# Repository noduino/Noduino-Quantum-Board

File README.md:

# Noduino-Quantum-Board
Noduino Quantum ESP32 Dev Board

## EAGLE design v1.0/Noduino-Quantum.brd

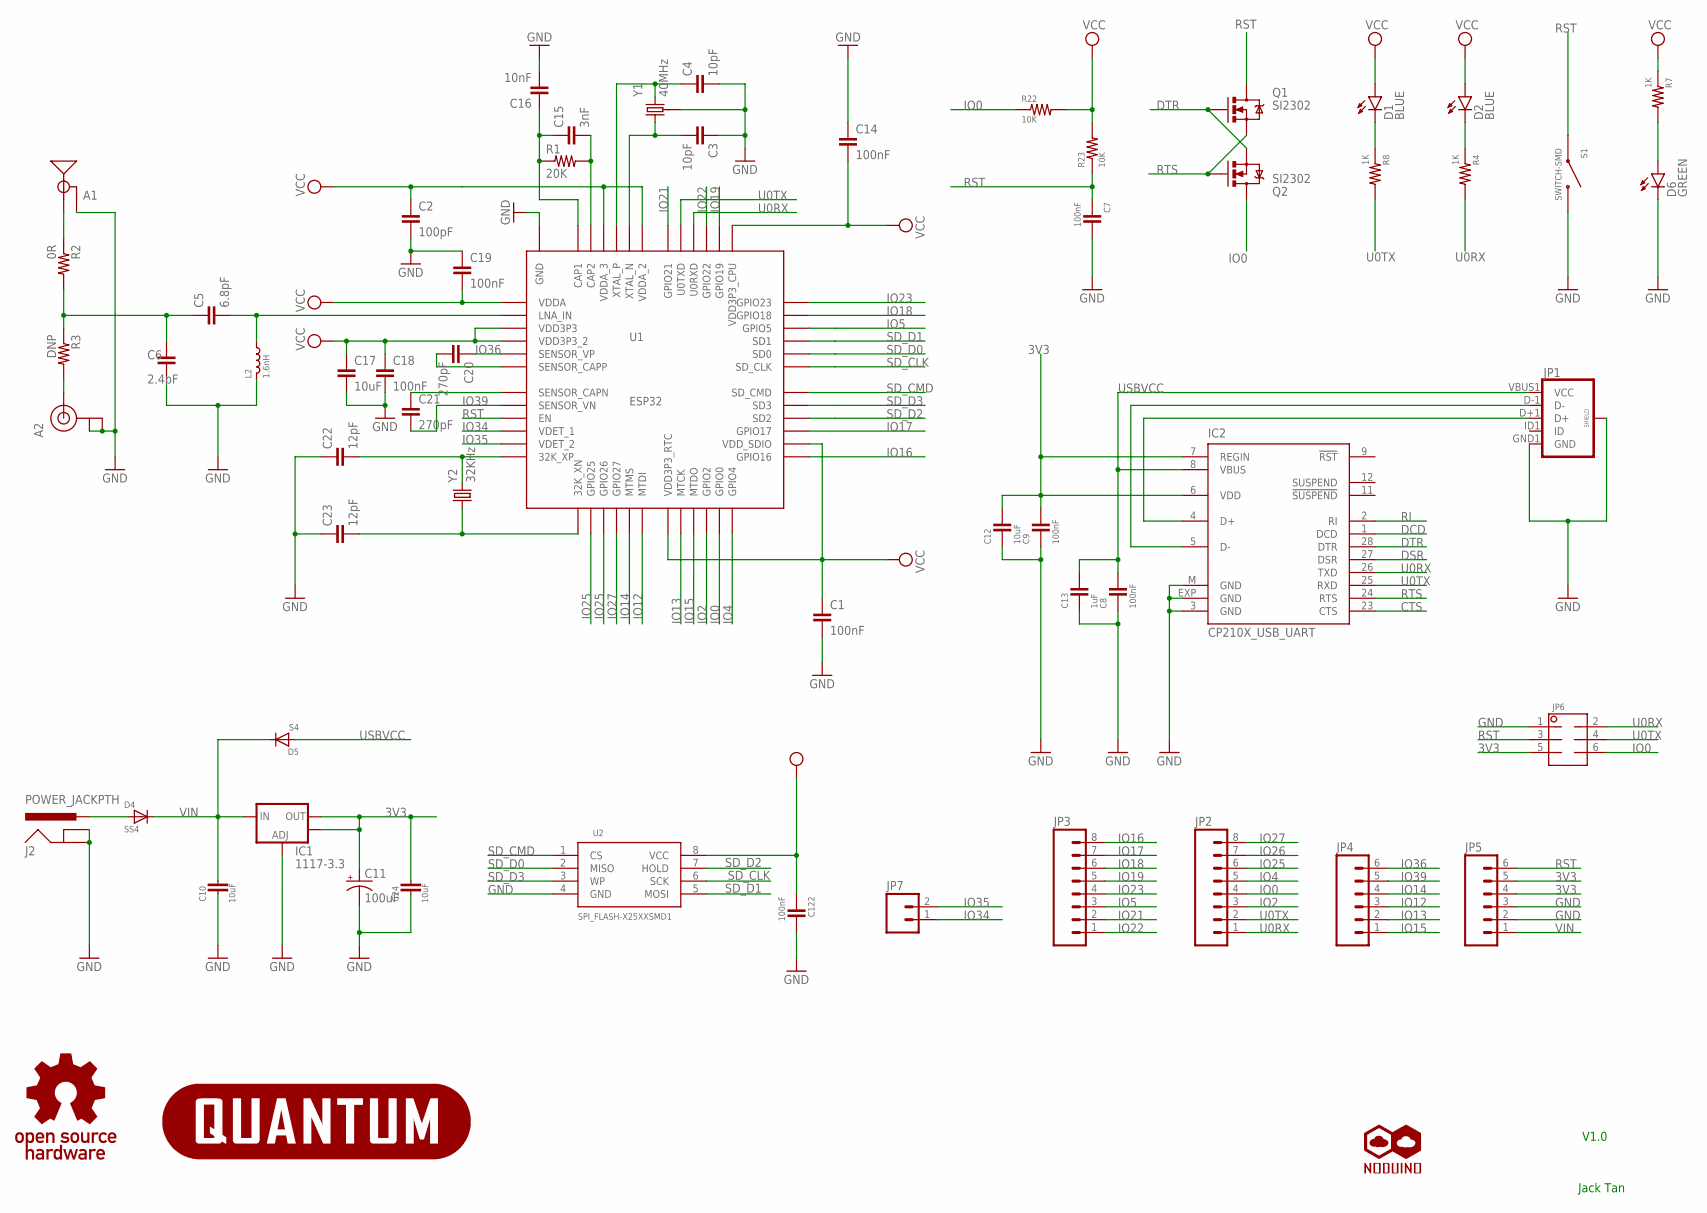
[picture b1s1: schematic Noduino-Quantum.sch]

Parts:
A1: ANTENNATPLACE; TRACE_ANTENNA_2.4GHZ_15.2MM_TPLACE
A2: U.FL
C1, C7, C14, C18, C19, C122: 100nF; 0402-CAP
C2: 100pF; 0402-CAP
C3, C4: 10pF; 0402-CAP
C5: 6.8pF; 0402-CAP
C6: 2.4pF; 0402-CAP
C8, C9: 100nF; 0603-CAP
C10, C24: 10uF; C1206
C11: 100uF; EIA3528
C12, C17: 10uF; 0603-CAP
C13: 1uF; 0603-CAP
C15: 3nF; 0402-CAP
C16: 10nF; 0402-CAP
C20, C21: 270pF; 0402-CAP
C22, C23: 12pF; 0402-CAP
D1, D2: BLUE; LED-0603
D4: SS4; DO214
D5: S4; SOD-323
D6: GREEN; LED-0603
IC1: 1117-3.3; SOT223
IC2: CP210X_USB_UART; MLP28
J2: POWER_JACKPTH; POWER_JACK_PTH
JP1: USB_MICROB_PLUG; MICROUSB-SMD-DIP
JP2, JP3: M081X08; 1X08
JP4, JP5: M06SIP; 1X06
JP6: M02X3; 2X3
JP7: M02PTH; 1X02
L2: 1.6nH; 0402-IND
Q1, Q2: SI2302; SOT23-3
R1: 20K; 0402-RES
R2: 0R; 0402-RES
R3: DNP; 0402-RES
R4, R7, R8: 1K; 0603-RES
R22: 10K; 0603-RES
R23: 10K; 0402-RES
S1: SWITCH-SMD; TACTILE-SWITCH-1101NE
U1: ESP32; QFN48-0.4MM
U2: SPI_FLASH-X25XXSMD1; SO08-EIAJ
U$1: NODUINO-LOGO-ALL; NODUINO-ALL-1
U$2: NODUINO-QUANTUM-LOGO
U$3: OPEN_HARDWARE_LOGO
Y1: 40MHz; 2520-CRY
Y2: 32KHz; CRYSTAL-32KHZ-MS3V

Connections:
3V3: C1.1, C2.1, C9.2, C11.A (+), C12.2, C14.2, C17.1, C18.1, C19.2, C24.1, C122.1, D1.A, D2.A, IC1.2 (OUT), IC1.4 (OUT), IC2.6 (VDD), IC2.7 (REGIN), JP5.4, JP5.5, JP6.5, R7.1, R22.2, R23.2, U1.1 (VDDA), U1.3 (VDD3P3), U1.4 (VDD3P3_2), U1.19 (VDD3P3_RTC), U1.26 (VDD_SDIO), U1.37 (VDD3P3_CPU), U1.43 (VDDA_2), U1.46 (VDDA_3), U2.8 (VCC)
CTS: IC2.23 (CTS)
DCD: IC2.1 (DCD)
DSR: IC2.27 (DSR)
DTR: IC2.28 (DTR), Q1.1 (G), Q2.2 (S)
GND: A1.GND, A2.P$1 (GND), A2.P$2 (GND), C1.2, C2.2, C3.1, C4.2, C6.2, C7.2, C8.1, C9.1, C10.2, C11.C (-), C12.1, C13.1, C14.1, C16.2, C17.2, C18.2, C19.1, C22.1, C23.1, C24.2, C122.2, D6.C, IC1.1 (ADJ), IC2.3 (GND), IC2.EXP (GND), IC2.M (GND), J2.GND, J2.GNDBREAK, JP1.GND1 (GND), JP1.P$1 (SHIELD), JP1.P$2 (SHIELD), JP1.P$3 (SHIELD), JP1.P$4 (SHIELD), JP5.2, JP5.3, JP6.1, L2.1 (X1), S1.P$1 (1), U1.EP (GND), U2.4 (GND), Y1.2 (GND), Y1.4 (GND)
IO0: JP2.4, JP6.6, Q2.3 (D), R22.1, U1.23 (GPIO0)
IO2: JP2.3, U1.22 (GPIO2)
IO4: JP2.5, U1.24 (GPIO4)
IO5: JP3.3, U1.34 (GPIO5)
IO12: JP4.3, U1.18 (MTDI)
IO13: JP4.2, U1.20 (MTCK)
IO14: JP4.4, U1.17 (MTMS)
IO15: JP4.1, U1.21 (MTDO)
IO16: JP3.8, U1.25 (GPIO16)
IO17: JP3.7, U1.27 (GPIO17)
IO18: JP3.6, U1.35 (GPIO18)
IO19: JP3.5, U1.38 (GPIO19)
IO21: JP3.2, U1.42 (GPIO21)
IO22: JP3.1, U1.39 (GPIO22)
IO23: JP3.4, U1.36 (GPIO23)
IO25: JP2.6, U1.14 (GPIO25)
IO26: JP2.7, U1.15 (GPIO26)
IO27: JP2.8, U1.16 (GPIO27)
IO34: JP7.1, U1.10 (VDET_1)
IO35: JP7.2, U1.11 (VDET_2)
IO36: C20.1, JP4.6, U1.5 (SENSOR_VP)
IO39: C21.2, JP4.5, U1.8 (SENSOR_VN)
LNA: C5.2, L2.2 (X2), U1.2 (LNA_IN)
unnamed: D1.C, R8.1
unnamed: C4.1, U1.45 (XTAL_P), Y1.3 (2)
unnamed: C3.2, U1.44 (XTAL_N), Y1.1
unnamed: IC2.4 (D+), JP1.D+1 (D+)
unnamed: A1.ANT (SIGNAL), R2.1
unnamed: IC2.5 (D-), JP1.D-1 (D-)
unnamed: C15.2, R1.2, U1.47 (CAP2)
unnamed: D2.C, R4.1
unnamed: D6.A, R7.2
unnamed: D4.A, J2.PWR
unnamed: C15.1, C16.1, R1.1, U1.48 (CAP1)
unnamed: A2.P$3 (SIGNAL), R3.2
unnamed: C5.1, C6.1, R3.1
unnamed: C21.1, U1.7 (SENSOR_CAPN)
unnamed: C20.2, U1.6 (SENSOR_CAPP)
unnamed: C22.2, U1.12 (32K_XP), Y2.P$2 (2)
unnamed: C23.2, U1.13 (32K_XN), Y2.P$1 (1)
RI: IC2.2 (RI)
RST: C7.1, JP5.6, JP6.3, Q1.3 (D), R23.1, S1.P$2 (2), U1.9 (EN)
RTS: IC2.24 (RTS), Q1.2 (S), Q2.1 (G)
SD_CLK: U1.31 (SD_CLK), U2.6 (SCK)
SD_CMD: U1.30 (SD_CMD), U2.1 (CS)
SD_D0: U1.32 (SD0), U2.2 (MISO)
SD_D1: U1.33 (SD1), U2.5 (MOSI)
SD_D2: U1.28 (SD2), U2.7 (HOLD)
SD_D3: U1.29 (SD3), U2.3 (WP)
U0RX: IC2.26 (TXD), JP2.1, JP6.2, R4.2, U1.40 (U0RXD)
U0TX: IC2.25 (RXD), JP2.2, JP6.4, R8.2, U1.41 (U0TXD)
USBVCC: C8.2, C13.2, D5.2 (A), IC2.8 (VBUS), JP1.VBUS1 (VCC)
VIN: C10.1, D4.C, D5.1 (C), IC1.3 (IN), JP5.1

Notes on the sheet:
Jack Tan
V1.0

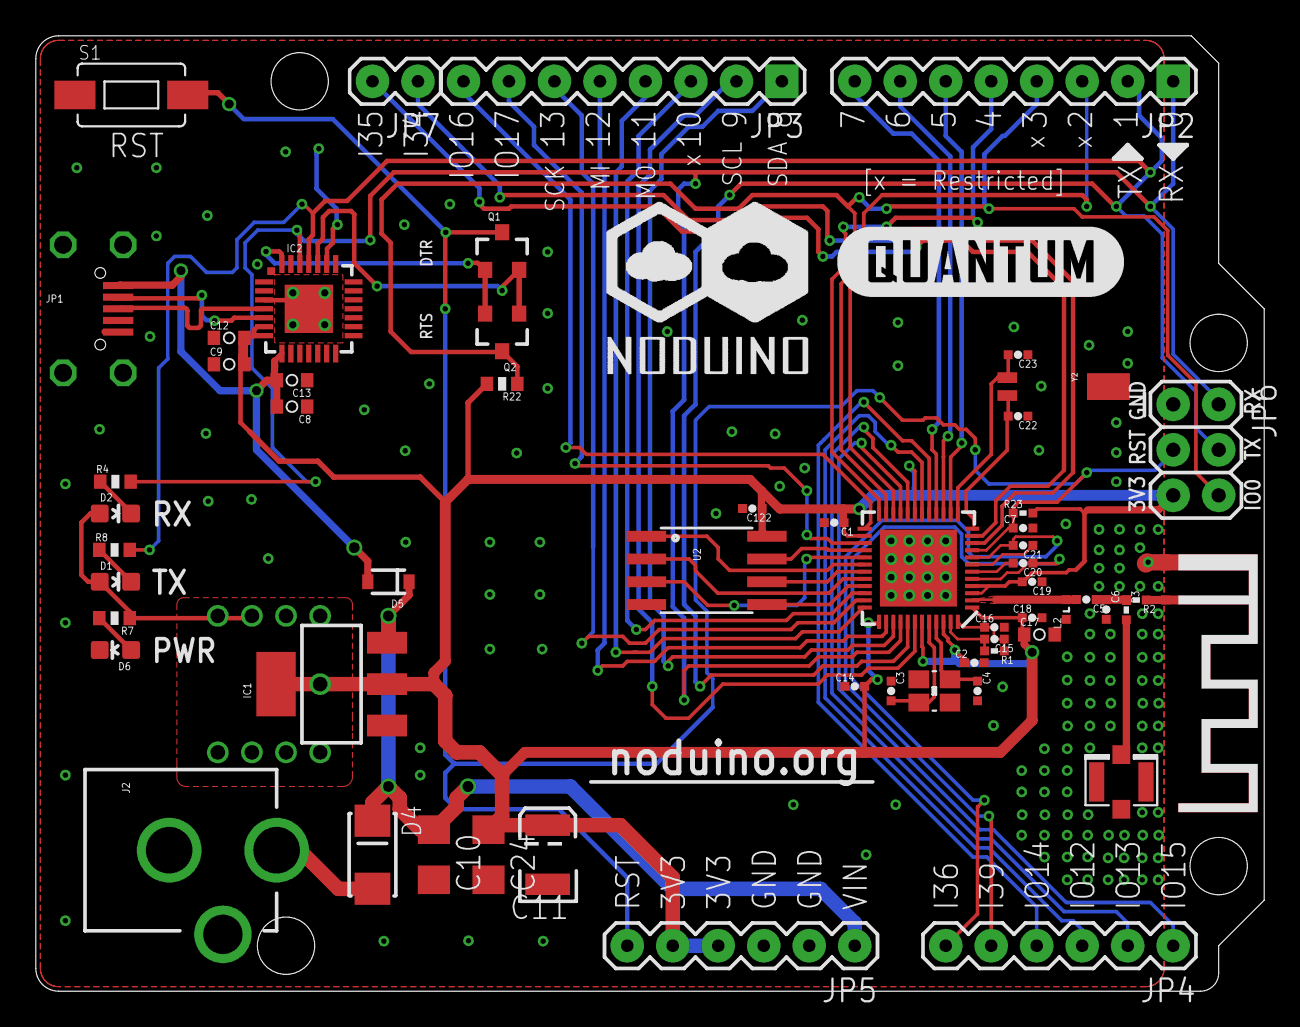
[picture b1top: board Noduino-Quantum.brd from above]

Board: 2 copper layers, 68.6 x 53.3 mm, 61 parts (1 on the bottom side), 55 nets.

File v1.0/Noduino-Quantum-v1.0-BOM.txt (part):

Partlist exported from C:/Users/Jack/Documents/eagle/Noduino/Quantum/V1.0/Noduino-Quantum.sch at 2016/11/1 20:32:44

Part Value                Device               Package                            Description                                                             PROD_ID    VALUE
A1                        ANTENNATPLACE        TRACE_ANTENNA_2.4GHZ_15.2MM_TPLACE Chip antenna                                                                            
A2   U.FL                 U.FL                 U.FL                               SMD antenna connector- WRL-09144                                        CONN-09193 U.FL
 
C1   100nF                0402-CAP             0402-CAP                                                                                                                   

C2   100pF                0402-CAP             0402-CAP                                                                                                                   

C3   15pF                 0402-CAP             0402-CAP                                                                                                                   
C4   15pF                 0402-CAP             0402-CAP                                                                                                                   

C5   6.8pF                0402-CAP             0402-CAP                                                                                                                   
C6   2.4pF                0402-CAP             0402-CAP                                                                                                                   

C7   100nF                0402-CAP             0402-CAP
                                                                                                                   
C8   100nF                0603-CAP             0603-CAP                                                                                                                   
C9   100nF                0603-CAP             0603-CAP
                                                                                                                   
C10  10uF                 CAP-C1206            C1206                              Capacitor                                                                               
C11  100uF                CAP_POL3528          EIA3528                            Capacitor Polarized
                                                                     
C12  10uF                 0603-CAP             0603-CAP                                                                                                                   
C13  1uF                  0603-CAP             0603-CAP 
                                                                                                                  
C14  100nF                0402-CAP             0402-CAP                                                                                                                   

C15  3nF                  0402-CAP             0402-CAP                                                                                                                   
C16  10nF                 0402-CAP             0402-CAP                                                                                                                   

C17  10uF                 0603-CAP             0603-CAP                                                                                                                   

C18  100nF                0402-CAP             0402-CAP                                                                                                                   
C19  100nF                0402-CAP             0402-CAP                                                                                                                   

C20  270pF                0402-CAP             0402-CAP                                                                                                                   
C21  270pF                0402-CAP             0402-CAP                                                                                                                   
C22  12pF                 0402-CAP             0402-CAP                                                                                                                   
C23  12pF                 0402-CAP             0402-CAP

C24  10uF                 CAP-C1206            C1206                              Capacitor    
                                                                           
C122 100nF                0402-CAP             0402-CAP                                                                                                                   

D1   BLUE                 LED-GREEN0603        LED-0603                           Various green LEDs                                                      DIO-00821  GREEN
D2   BLUE                 LED-GREEN0603        LED-0603                           Various green LEDs                                                      DIO-00821  GREEN

D4   S7                   DIODEHV              DO214                              Diode                                                                                   
D5   S4                   DIODESOD             SOD-323                            Diode                                                                                   

D6   GREEN                LED-GREEN0603        LED-0603                           Various green LEDs                                                      DIO-00821  GREEN

IC1  1117-3.3             AMS1117SOT223        SOT223                             Voltage Regulator LM1117                                                                
IC2  CP210X_USB_UART      CP210X_USB_UART      MLP28                              Single-Chip USB to UART Bridge
                                                         
J2   POWER_JACKPTH        POWER_JACKPTH        POWER_JACK_PTH                     Power Jack                                                                              
JP1                       USB_MICROB_PLUG      MICROUSB-SMD-DIP                   USB Micro-B connectors 
                                                                 
JP2  M081X08              M081X08              1X08                               Header 8                                                                                
JP3  M081X08              M081X08              1X08                               Header 8                                                                                
JP4  M06SIP               M06SIP               1X06                               Header 6                                                                                
JP5  M06SIP               M06SIP               1X06                               Header 6                                                                                
JP6  M02X3                M02X3                2X3                                                                                                                        
JP7                       M02PTH               1X02                               Header 2
                                                                                
L2   1.6nH                INDUCTOR0402         0402-IND
                                                                                                                   
Q1   SI2302               -MOSFET-N-SMD        SOT23-3                                                                                                                    
Q2   SI2302               -MOSFET-N-SMD        SOT23-3
                                                                                                                   
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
